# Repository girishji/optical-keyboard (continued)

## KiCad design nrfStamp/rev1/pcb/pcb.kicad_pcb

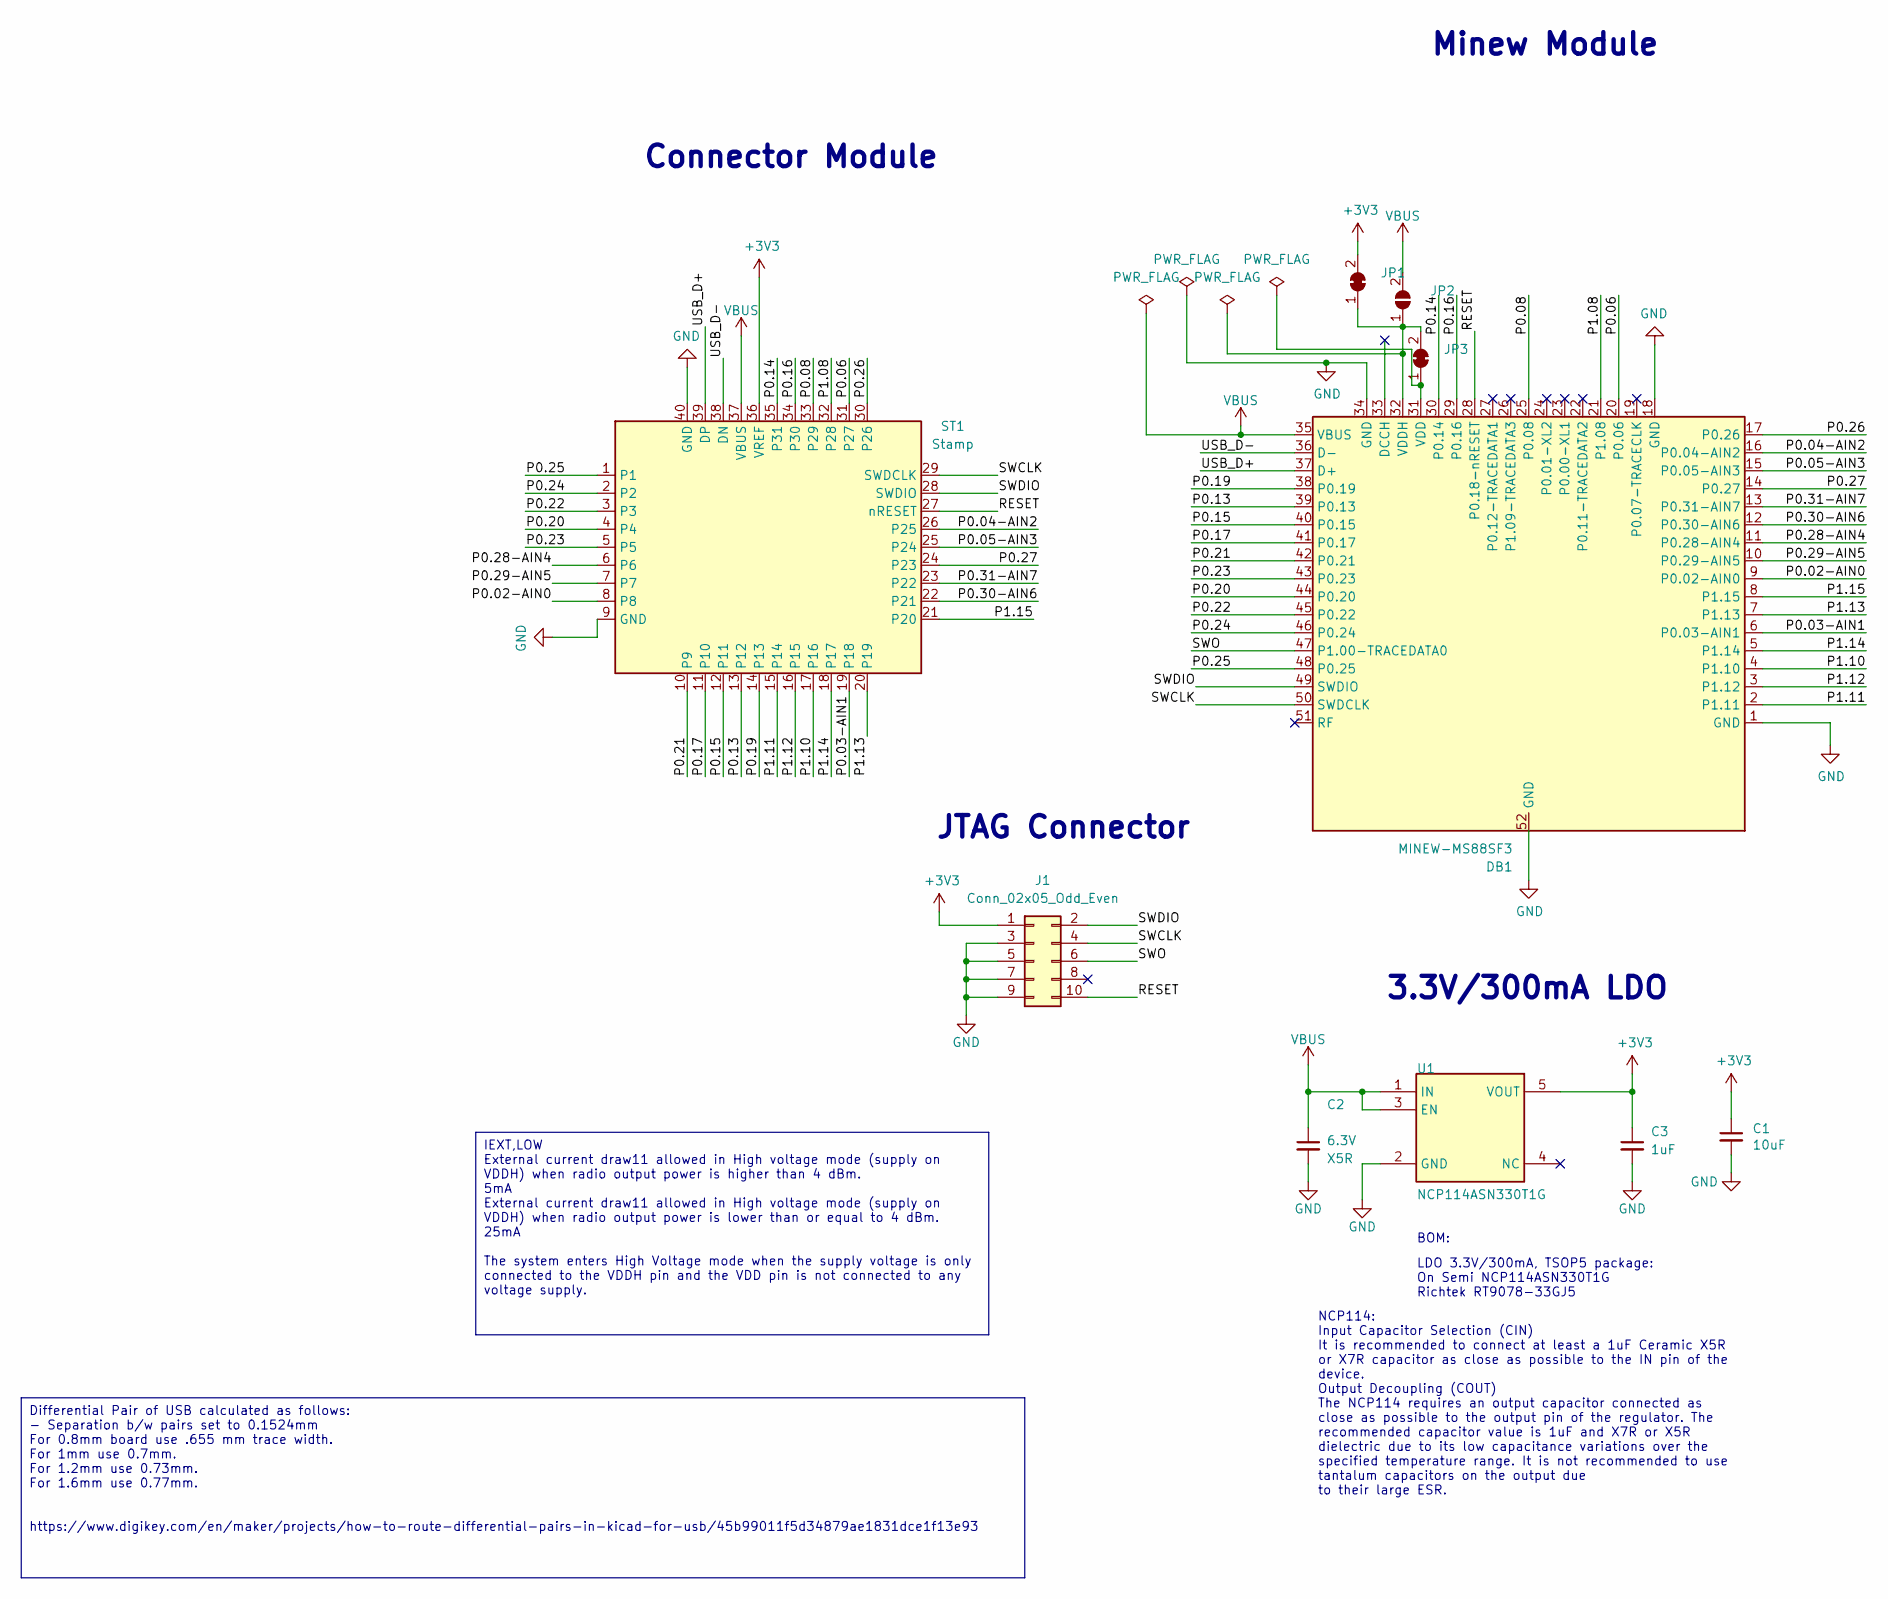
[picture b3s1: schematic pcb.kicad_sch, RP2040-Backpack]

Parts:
C1: 10uF; C_0603_1608Metric; MPN CC0603MRX5R8BB106; LCSC C596327
C2: 2.2uF; C_0603_1608Metric; VOLTAGE RATING 6.3V; TOLERANCE TBD; MPN CL05A225MQ5NNNC; LCSC C107371
C3: 1uF; C_0603_1608Metric; MPN CC0402KRX5R6BB105; LCSC C106254
DB1: MINEW-MS88SF3
J1: Conn_02x05_Odd_Even; PinHeader_2x05_P1.27mm_Horizontal
JP1, JP3: SolderJumper_2_Bridged; SolderJumper-2_Bridged_Pad
JP2: SolderJumper_2_Open; SolderJumper-2_Open_Pad
ST1: Stamp
U1: NCP114ASN330T1G; TSOP-5_1.65x3.05mm_P0.95mm; MPN NCP114ASN330T1G; LCSC C457666

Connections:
+3V3: C1.1, C3.1, J1.1, JP1.2 (B), ST1.36 (VREF), U1.5 (VOUT)
/P0.02-AIN0: DB1.9 (P0.02-AIN0), ST1.8
/P0.03-AIN1: DB1.6 (P0.03-AIN1), ST1.19 (P18)
/P0.04-AIN2: DB1.16 (P0.04-AIN2), ST1.26 (P25)
/P0.05-AIN3: DB1.15 (P0.05-AIN3), ST1.25 (P24)
/P0.06: DB1.20 (P0.06), ST1.31 (P27)
/P0.08: DB1.25 (P0.08), ST1.33 (P29)
/P0.13: DB1.39 (P0.13), ST1.13 (P12)
/P0.14: DB1.30 (P0.14), ST1.35 (P31)
/P0.15: DB1.40 (P0.15), ST1.12 (P11)
/P0.16: DB1.29 (P0.16), ST1.34 (P30)
/P0.17: DB1.41 (P0.17), ST1.11 (P10)
/P0.19: DB1.38 (P0.19), ST1.14 (P13)
/P0.20: DB1.44 (P0.20), ST1.4
/P0.21: DB1.42 (P0.21), ST1.10 (P9)
/P0.22: DB1.45 (P0.22), ST1.3
/P0.23: DB1.43 (P0.23), ST1.5
/P0.24: DB1.46 (P0.24), ST1.2
/P0.25: DB1.48 (P0.25), ST1.1
/P0.26: DB1.17 (P0.26), ST1.30 (P26)
/P0.27: DB1.14 (P0.27), ST1.24 (P23)
/P0.28-AIN4: DB1.11 (P0.28-AIN4), ST1.6
/P0.29-AIN5: DB1.10 (P0.29-AIN5), ST1.7
/P0.30-AIN6: DB1.12 (P0.30-AIN6), ST1.22 (P21)
/P0.31-AIN7: DB1.13 (P0.31-AIN7), ST1.23 (P22)
/P1.08: DB1.21 (P1.08), ST1.32 (P28)
/P1.10: DB1.4 (P1.10), ST1.17 (P16)
/P1.11: DB1.2 (P1.11), ST1.15 (P14)
/P1.12: DB1.3 (P1.12), ST1.16 (P15)
/P1.13: DB1.7 (P1.13), ST1.20 (P19)
/P1.14: DB1.5 (P1.14), ST1.18 (P17)
/P1.15: DB1.8 (P1.15), ST1.21 (P20)
/RESET: DB1.28 (P0.18-nRESET), J1.10, ST1.27 (nRESET)
/SWCLK: DB1.50 (SWDCLK), J1.4, ST1.29 (SWDCLK)
/SWDIO: DB1.49 (SWDIO), J1.2, ST1.28 (SWDIO)
/SWO: DB1.47 (P1.00-TRACEDATA0), J1.6
/USB_D+: DB1.37 (D+), ST1.39 (DP)
/USB_D-: DB1.36 (D-), ST1.38 (DN)
GND: C1.2, C2.2, C3.2, DB1.1 (GND), DB1.18 (GND), DB1.34 (GND), DB1.52 (GND), J1.3, J1.5, J1.7, J1.9, ST1.9 (GND), ST1.40 (GND), U1.2 (GND)
unnamed: DB1.31 (VDD), JP3.1 (A)
unnamed: DB1.32 (VDDH), JP1.1 (A), JP2.1 (A), JP3.2 (B)
VBUS: C2.1, DB1.35 (VBUS), JP2.2 (B), ST1.37 (VBUS), U1.1 (IN), U1.3 (EN)

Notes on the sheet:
IEXT,LOW External current draw11 allowed in High voltage mode (supply on VDDH) when radio output power is higher than 4 dBm. 5mA External current draw11 allowed in High voltage mode (supply on VDDH) when radio output power is lower than or equal to 4 dBm. 25mA The system enters High Voltage mode wh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
Differential Pair of USB calculated as follows: - Separation b/w pairs set to 0.1524mm For 0.8mm board use .655 mm trace width. For 1mm use 0.7mm. For 1.2mm use 0.73mm. For 1.6mm use 0.77mm. https://www.digikey.com/en/maker/projects/how-to-route-differential-pairs-in-kicad-for-usb/45b99011f5d34879a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
3.3V/300mA LDO
JTAG Connector
Connector Module
BOM:
LDO 3.3V/300mA, TSOP5 package: On Semi NCP114ASN330T1G Richtek RT9078-33GJ5
Minew Module
NCP114: Input Capacitor Selection (CIN) It is recommended to connect at least a 1uF Ceramic X5R or X7R capacitor as close as possible to the IN pin of the device. Output Decoupling (COUT) The NCP114 requires an output capacitor connected as close as possible to the output pin of the regulator. The 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

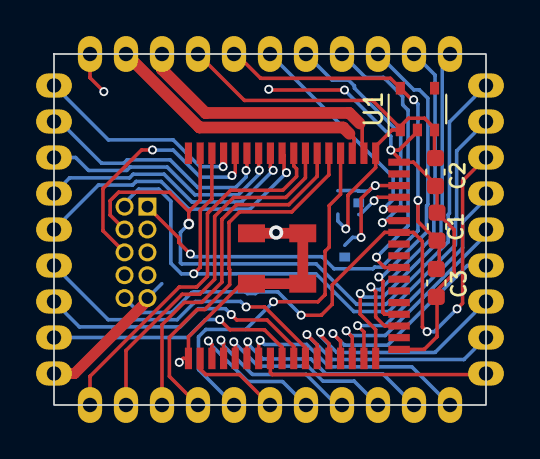
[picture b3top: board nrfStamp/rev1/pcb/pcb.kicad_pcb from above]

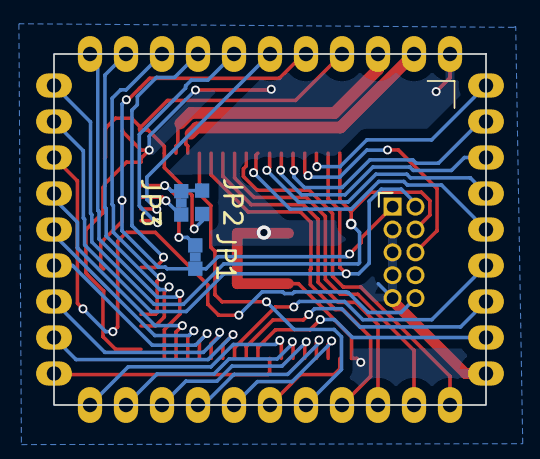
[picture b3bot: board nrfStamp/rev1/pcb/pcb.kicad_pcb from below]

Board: 2 copper layers, 24.0 x 19.5 mm, 10 parts (4 on the bottom side), 42 nets.

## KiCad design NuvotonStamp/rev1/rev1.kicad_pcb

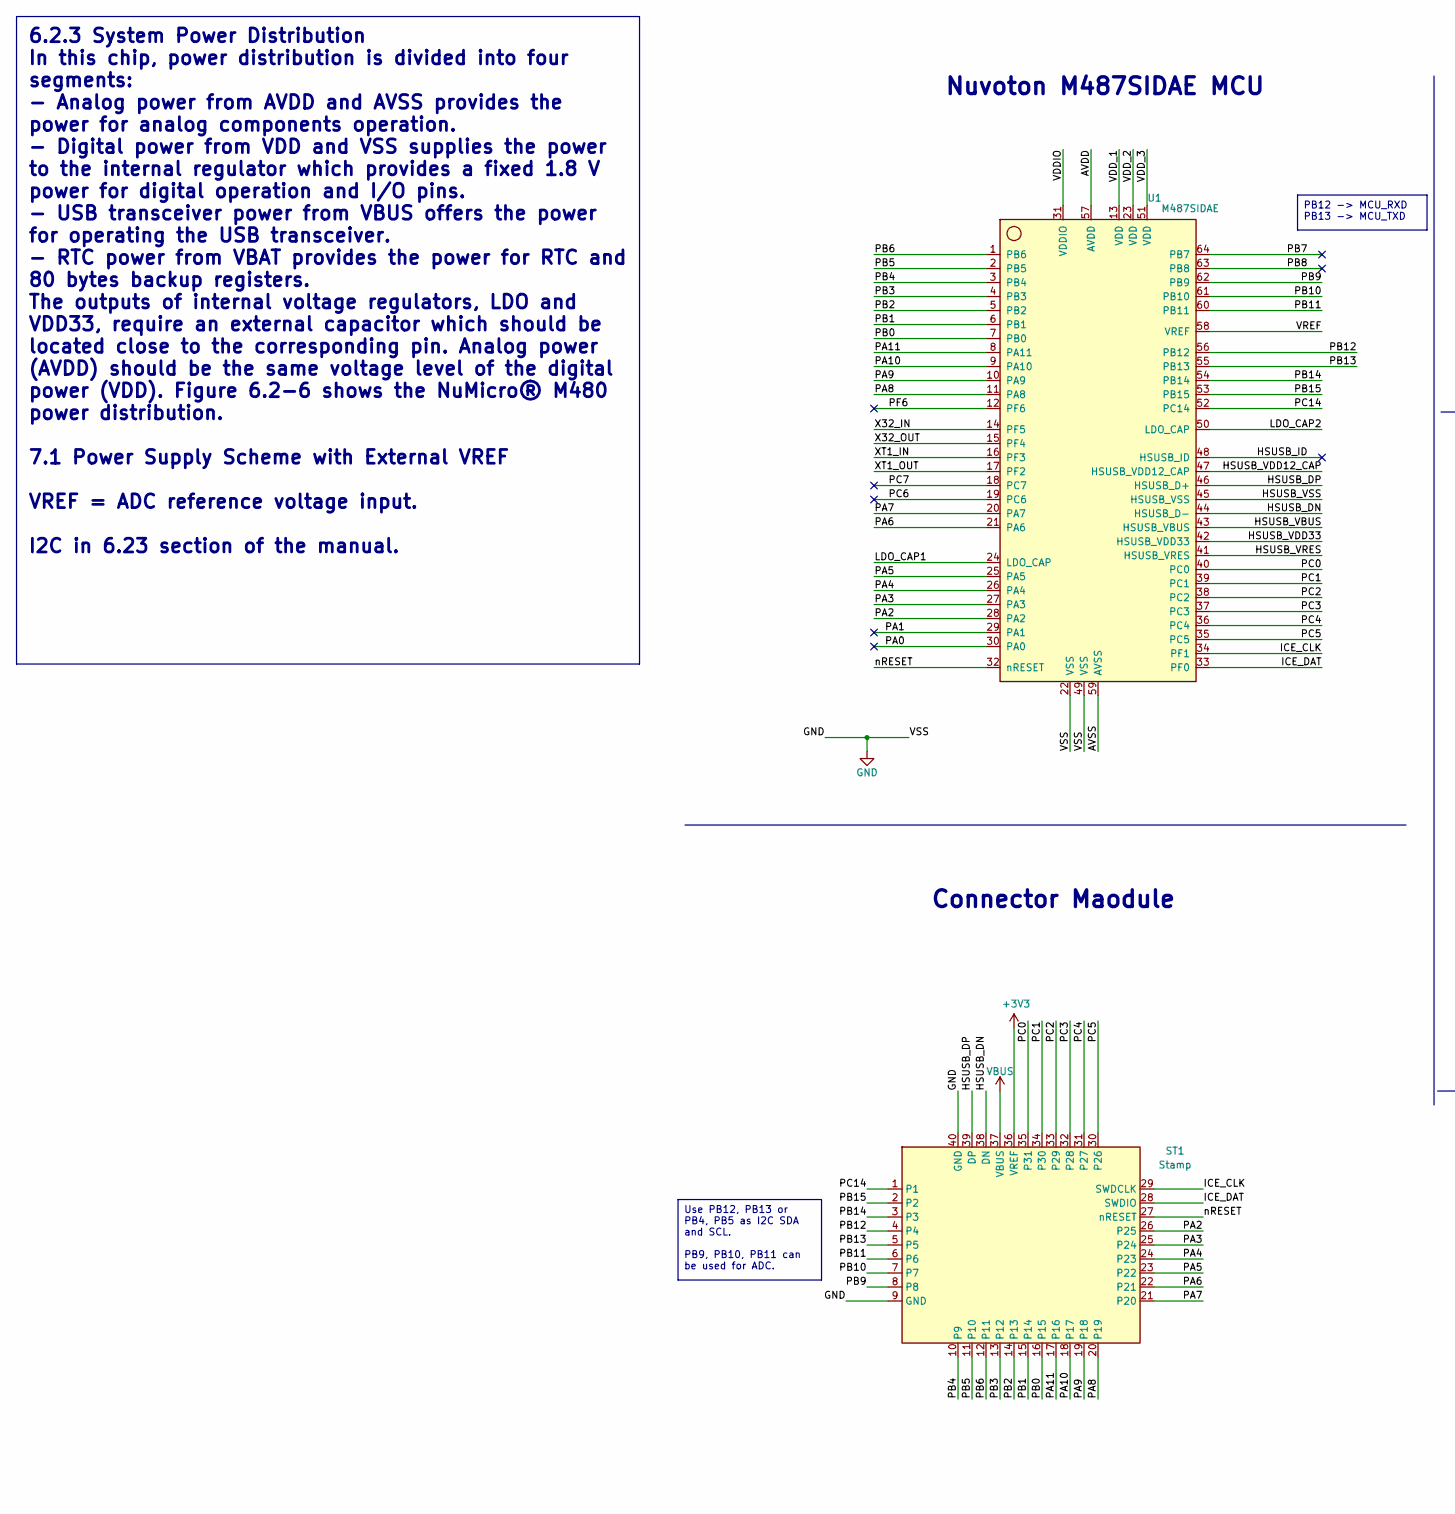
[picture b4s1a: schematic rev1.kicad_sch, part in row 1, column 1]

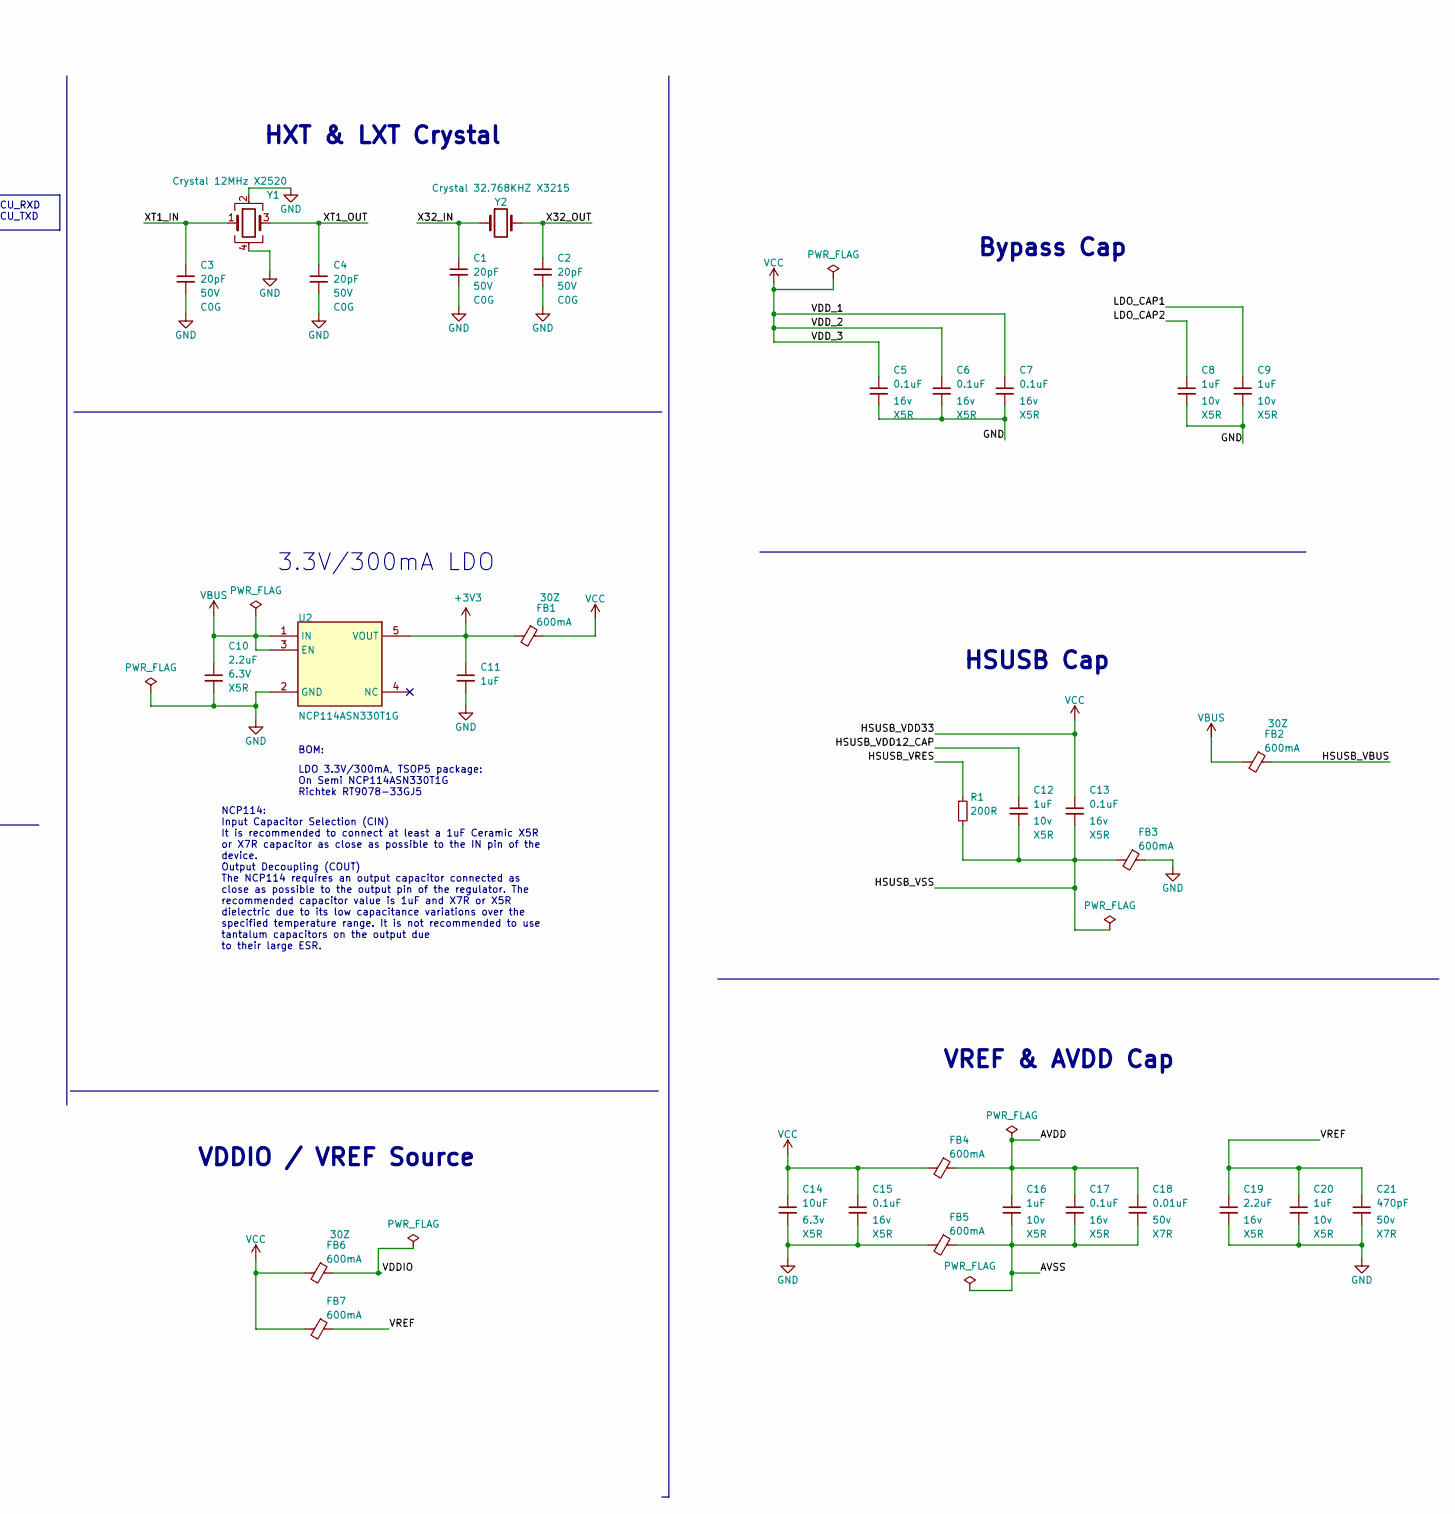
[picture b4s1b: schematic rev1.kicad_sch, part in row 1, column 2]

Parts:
C1, C2, C3, C4: 20pF; C_0402_1005Metric; Voltage Rating 50V; MPN CL05C200JB5NNNC; LCSC C32950
C5, C6, C7, C13, C15, C17: 0.1uF; C_0402_1005Metric; VOLTAGE RATING 16v; MPN CL05B104KO5NNNC; LCSC C1525
C8, C9: 1uF; C_0402_1005Metric; VOLTAGE RATING 10v
C10: 2.2uF; C_0402_1005Metric; VOLTAGE RATING 6.3V; TOLERANCE TBD; MPN CL05A225MQ5NNNC; LCSC C107371
C11: 1uF; C_0402_1005Metric; MPN CC0402KRX5R6BB105; LCSC C106254
C12, C16, C20: 1uF; C_0402_1005Metric; VOLTAGE RATING 10v; MPN CL05A105KP5NNNC; LCSC C14445
C14: 10uF; C_0402_1005Metric; VOLTAGE RATING 6.3v; MPN CL05A106MQ5NUNC; LCSC C15525
C18: 0.01uF; C_0402_1005Metric; VOLTAGE RATING 50v; MPN CL05B103KB5NNNC; LCSC C15195
C19: 2.2uF; C_0402_1005Metric; VOLTAGE RATING 16v; MPN CL05A225KO5NQNC; LCSC C170151
C21: 470pF; C_0402_1005Metric; VOLTAGE RATING 50v; MPN CL05B471KB5NNNC; LCSC C26412
FB1, FB2, FB6: 30Z; R_0402_1005Metric; MPN BLM15AX221SN1D; LCSC C76885
FB3, FB4, FB5, FB7: FerriteBead_Small; R_0402_1005Metric; MPN BLM15AX221SN1D; LCSC C76885
R1: 200R; R_0402_1005Metric; Power Rating 62.5mW; MPN RC0402FR-07200RL; LCSC C114764
ST1: Stamp
U1: M487SIDAE; LQFP-64_7x7mm_P0.4mm
U2: NCP114ASN330T1G; TSOP-5_1.65x3.05mm_P0.95mm; MPN NCP114ASN330T1G; LCSC C457666
Y1: Crystal 12MHz X2520; Crystal_SMD_2520-4Pin_2.5x2.0mm
Y2: Crystal 32.768KHZ X3215; Crystal_SMD_3215-2Pin_3.2x1.5mm; MPN Q13FC1350000200; LCSC C48615

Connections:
+3V3: C11.1, FB1.2, ST1.36 (VREF), U2.5 (VOUT)
/AVDD: C16.1, C17.1, C18.1, FB4.1, U1.57 (AVDD)
/AVSS: C16.2, C17.2, C18.2, FB5.1, U1.59 (AVSS)
/HSUSB_DN: ST1.38 (DN), U1.44 (HSUSB_D-)
/HSUSB_DP: ST1.39 (DP), U1.46 (HSUSB_D+)
/HSUSB_ID: U1.48 (HSUSB_ID)
/HSUSB_VBUS: FB2.1, U1.43 (HSUSB_VBUS)
/HSUSB_VDD12_CAP: C12.1, U1.47 (HSUSB_VDD12_CAP)
/HSUSB_VRES: R1.1, U1.41 (HSUSB_VRES)
/HSUSB_VSS: C12.2, C13.2, FB3.2, R1.2, U1.45 (HSUSB_VSS)
/ICE_CLK: ST1.29 (SWDCLK), U1.34 (PF1)
/ICE_DAT: ST1.28 (SWDIO), U1.33 (PF0)
/LDO_CAP1: C9.1, U1.24 (LDO_CAP)
/LDO_CAP2: C8.1, U1.50 (LDO_CAP)
/PA0: U1.30 (PA0)
/PA1: U1.29 (PA1)
/PA2: ST1.26 (P25), U1.28 (PA2)
/PA3: ST1.25 (P24), U1.27 (PA3)
/PA4: ST1.24 (P23), U1.26 (PA4)
/PA5: ST1.23 (P22), U1.25 (PA5)
/PA6: ST1.22 (P21), U1.21 (PA6)
/PA7: ST1.21 (P20), U1.20 (PA7)
/PA8: ST1.20 (P19), U1.11 (PA8)
/PA9: ST1.19 (P18), U1.10 (PA9)
/PA10: ST1.18 (P17), U1.9 (PA10)
/PA11: ST1.17 (P16), U1.8 (PA11)
/PB0: ST1.16 (P15), U1.7 (PB0)
/PB1: ST1.15 (P14), U1.6 (PB1)
/PB2: ST1.14 (P13), U1.5 (PB2)
/PB3: ST1.13 (P12), U1.4 (PB3)
/PB4: ST1.10 (P9), U1.3 (PB4)
/PB5: ST1.11 (P10), U1.2 (PB5)
/PB6: ST1.12 (P11), U1.1 (PB6)
/PB7: U1.64 (PB7)
/PB8: U1.63 (PB8)
/PB9: ST1.8, U1.62 (PB9)
/PB10: ST1.7, U1.61 (PB10)
/PB11: ST1.6, U1.60 (PB11)
/PB12: ST1.4, U1.56 (PB12)
/PB13: ST1.5, U1.55 (PB13)
/PB14: ST1.3, U1.54 (PB14)
/PB15: ST1.2, U1.53 (PB15)
/PC0: ST1.35 (P31), U1.40 (PC0)
/PC1: ST1.34 (P30), U1.39 (PC1)
/PC2: ST1.33 (P29), U1.38 (PC2)
/PC3: ST1.32 (P28), U1.37 (PC3)
/PC4: ST1.31 (P27), U1.36 (PC4)
/PC5: ST1.30 (P26), U1.35 (PC5)
/PC6: U1.19 (PC6)
/PC7: U1.18 (PC7)
/PC14: ST1.1, U1.52 (PC14)
/PF6: U1.12 (PF6)
/VDDIO: FB6.1, U1.31 (VDDIO)
/VREF: C19.1, C20.1, C21.1, FB7.1, U1.58 (VREF)
/X32_IN: C1.1, U1.14 (PF5), Y2.1
/X32_OUT: C2.1, U1.15 (PF4), Y2.2
/XT1_IN: C3.1, U1.16 (PF3), Y1.1
/XT1_OUT: C4.1, U1.17 (PF2), Y1.3
/nRESET: ST1.27 (nRESET), U1.32 (nRESET)
GND: C1.2, C2.2, C3.2, C4.2, C5.2, C6.2, C7.2, C8.2, C9.2, C10.2, C11.2, C14.2, C15.2, C19.2, C20.2, C21.2, FB3.1, FB5.2, ST1.9 (GND), ST1.40 (GND), U1.22 (VSS), U1.49 (VSS), U2.2 (GND), Y1.2, Y1.4
VBUS: C10.1, FB2.2, ST1.37 (VBUS), U2.1 (IN), U2.3 (EN)
VCC: C5.1, C6.1, C7.1, C13.1, C14.1, C15.1, FB1.1, FB4.2, FB6.2, FB7.2, U1.13 (VDD), U1.23 (VDD), U1.42 (HSUSB_VDD33), U1.51 (VDD)

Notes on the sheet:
PB12 -> MCU_RXD PB13 -> MCU_TXD
Use PB12, PB13 or PB4, PB5 as I2C SDA and SCL. PB9, PB10, PB11 can be used for ADC.
6.2.3 System Power Distribution In this chip, power distribution is divided into four segments: - Analog power from AVDD and AVSS provides the power for analog components operation. - Digital power from VDD and VSS supplies the power to the internal regulator which provides a fixed 1.8 V power for 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
BOM:
3.3V/300mA LDO
Connector Maodule
VREF & AVDD Cap
LDO 3.3V/300mA, TSOP5 package: On Semi NCP114ASN330T1G Richtek RT9078-33GJ5
HSUSB Cap
Nuvoton M487SIDAE MCU
NCP114: Input Capacitor Selection (CIN) It is recommended to connect at least a 1uF Ceramic X5R or X7R capacitor as close as possible to the IN pin of the device. Output Decoupling (COUT) The NCP114 requires an output capacitor connected as close as possible to the output pin of the regulator. The 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
HXT & LXT Crystal
Bypass Cap
VDDIO / VREF Source

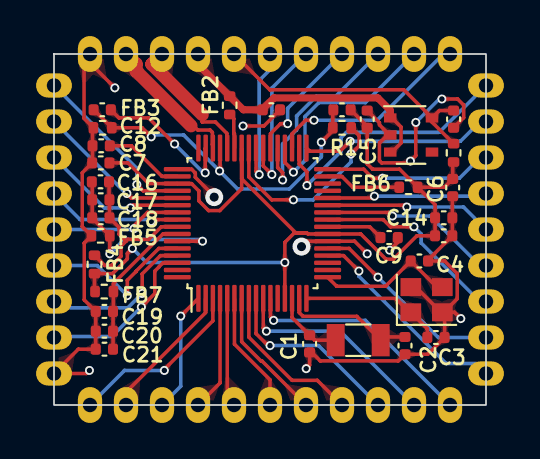
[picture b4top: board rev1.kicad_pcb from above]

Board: 2 copper layers, 24.0 x 19.5 mm, 34 parts (0 on the bottom side), 54 nets.

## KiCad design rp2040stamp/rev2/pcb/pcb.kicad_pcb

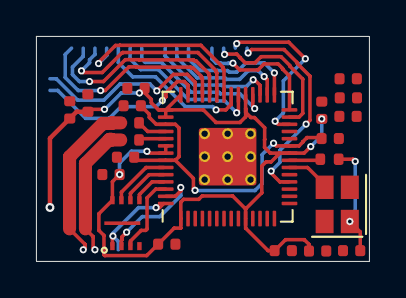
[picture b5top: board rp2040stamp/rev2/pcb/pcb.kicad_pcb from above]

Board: 2 copper layers, 18.5 x 12.5 mm, 23 parts (0 on the bottom side), 35 nets.

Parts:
C1, C2, C3, C4, C5, C6, C7, C8, C9, C12: 100nF; C_0402_1005Metric
C10, C11: 1uF; C_0402_1005Metric
C13: 2.2uF; C_0402_1005Metric
C14, C15: 15pF; C_0402_1005Metric
DB1: MINEW-MS88SF3; MINEW-MS88SF3-Daughter-Board
JLC1: JLC_Order_Num
R1, R2: 27R; R_0402_1005Metric
R3: 1k; R_0402_1005Metric
U1: RP2040; RP2040-QFN-56
U2: Memory_Flash_W25Q64_XSON; 8-USON-Handsolder
X1: 12.000MHz; Crystal_SMD_2520-4Pin_2.5x2.0mm-Handsolder

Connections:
+1V1: C1.1, C2.1, C10.1, U1.23 (DVDD), U1.45 (VREG_VOUT), U1.50 (DVDD)
+3V3: C3.1, C4.1, C5.1, C6.1, C7.1, C8.1, C9.1, C11.1, C12.1, C13.1, DB1.31 (VDD), U1.1 (IOVDD), U1.10 (IOVDD), U1.22 (IOVDD), U1.33 (IOVDD), U1.42 (IOVDD), U1.43 (ADC_AVDD), U1.44 (VREG_IN), U1.48 (USB_VDD), U1.49 (IOVDD), U2.8 (VCC)
/D+: R1.1, U1.47 (USB_DP)
/D-: R2.1, U1.46 (USB_DM)
/GPIO0: DB1.40 (P0.15), U1.2 (GPIO0)
/GPIO15: DB1.2 (P1.11), U1.18 (GPIO15)
/GPIO18: DB1.7 (P1.13), U1.29 (GPIO18)
/GPIO19: DB1.8 (P1.15), U1.30 (GPIO19)
/GPIO20: DB1.9 (P0.02-AIN0), U1.31 (GPIO20)
/GPIO21: DB1.11 (P0.28-AIN4), U1.32 (GPIO21)
/GPIO22: DB1.12 (P0.30-AIN6), U1.34 (GPIO22)
/GPIO23: DB1.13 (P0.31-AIN7), U1.35 (GPIO23)
/GPIO24: DB1.14 (P0.27), U1.36 (GPIO24)
/GPIO25: DB1.15 (P0.05-AIN3), U1.37 (GPIO25)
/GPIO26: DB1.16 (P0.04-AIN2), U1.38 (GPIO26_ADC0)
/GPIO27: DB1.17 (P0.26), U1.39 (GPIO27_ADC1)
/GPIO28: DB1.20 (P0.06), U1.40 (GPIO28_ADC2)
/GPIO29: DB1.21 (P1.08), U1.41 (GPIO29_ADC3)
/QSPI_SCLK: U1.52 (QSPI_SCLK), U2.6 (CLK)
/QSPI_SD0: U1.53 (QSPI_SD0), U2.5 (DI_(IO0))
/QSPI_SD1: U1.55 (QSPI_SD1), U2.2 (DO_(IO1))
/QSPI_SD2: U1.54 (QSPI_SD2), U2.3 (~WP_(IO2))
/QSPI_SD3: U1.51 (QSPI_SD3), U2.7 (~HOLD_(IO3))
/QSPI_SS: DB1.39 (P0.13), U1.56 (QSPI_SS), U2.1 (~{CS)
/RUN: DB1.3 (P1.12), U1.26 (RUN)
/SWCLK: DB1.50 (SWDCLK), U1.24 (SWCLK)
/SWD: DB1.49 (SWDIO), U1.25 (SWD)
/USB_D+: DB1.37 (D+), R1.2
/USB_D-: DB1.36 (D-), R2.2
/XIN: C15.1, U1.20 (XIN), X1.3
/XOUT: R3.1, U1.21 (XOUT)
GND: C1.2, C2.2, C3.2, C4.2, C5.2, C6.2, C7.2, C8.2, C9.2, C10.2, C11.2, C12.2, C13.2, C14.2, C15.2, DB1.1 (GND), DB1.18 (GND), DB1.34 (GND), DB1.56 (GND), U1.19 (TESTEN), U1.57 (GND), U2.4 (GND), U2.9 (EP), X1.2, X1.4
unnamed: C14.1, R3.2, X1.1
SCL: DB1.5 (P1.14), U1.28 (GPIO17)
SDA: DB1.4 (P1.10), U1.27 (GPIO16)

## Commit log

2022-10-13 First commit
    A .DS_Store
    A Giri_Library.kicad_sym
    A Giri_Library.pretty/Keychron_Optical_Switch_1u.kicad_mod
    A Giri_Library.pretty/SMTSO_M2.kicad_mod
    A Giri_Library.pretty/Switch_Cutout_LoPro.kicad_mod
    A Giri_Library.pretty/Switch_Cutout_LoPro_2.25u_Faulty.kicad_mod
2022-10-14 M .gitignore M lopro/drawborderk.py M lopro/pcb/pcb.kicad_pcb M lopro/pcb/pcb.kicad_sch M lopro/place_fp.py
2022-10-14 removed zip
    M .gitignore
    D lopro/pcb/pcb-backups/pcb-2022-10-13_182503.zip
    D lopro/pcb/pcb-backups/pcb-2022-10-13_183133.zip
    D lopro/pcb/pcb-backups/pcb-2022-10-13_202552.zip
    D lopro/pcb/pcb-backups/pcb-2022-10-13_212841.zip
    D lopro/pcb/pcb-backups/pcb-2022-10-13_213616.zip
2022-10-14 A lopro/pcb/.gitignore
2022-10-14 updated
    M lopro/drawborderk.py
2022-10-14 bug fix
    M lopro/drawborderk.py
2022-10-14 added tracks
    M Giri_Library.pretty/Keychron_Optical_Switch_1u.kicad_mod
    D lopro/drawborder.py
    M lopro/pcb/pcb.kicad_pcb
    M lopro/pcb/pcb.kicad_prl
    M lopro/place_fp.py
2022-10-15 add tracks
    M Giri_Library.kicad_sym
    M Giri_Library.pretty/Keychron_Optical_Switch_1u.kicad_mod
    A lopro/pcb/LED-Driver.kicad_sch
    M lopro/pcb/pcb.kicad_pcb
    M lopro/pcb/pcb.kicad_sch
    M lopro/place_fp.py
2022-10-16 gitignore
    A lopro/switch-plate/.gitignore
2022-10-16 add 1-1/4 key
    M lopro/place_fp.py
2022-10-17 add new pcb for rp2040 30 pin mcu
    R lopro/drawborderk.py -> lopro/6banks/drawborderk.py
    R lopro/pcb/.gitignore -> lopro/6banks/pcb/.gitignore
    R lopro/pcb/LED-Driver.kicad_sch -> lopro/6banks/pcb/LED-Driver.kicad_sch
    R lopro/pcb/fp-lib-table -> lopro/6banks/pcb/fp-lib-table
    R lopro/pcb/pcb.kicad_pcb -> lopro/6banks/pcb/pcb.kicad_pcb
    R lopro/pcb/pcb.kicad_prl -> lopro/6banks/pcb/pcb.kicad_prl
2022-10-27 Added new keyboard
    D .DS_Store
    A giri-kicad-lib/.gitignore
    R Giri_Library.kicad_sym -> giri-kicad-lib/switches.kicad_sym
    A giri-kicad-lib/switches_lib.pretty/C_0402_1005Metric.kicad_mod
    A giri-kicad-lib/switches_lib.pretty/C_0603_1608Metric.kicad_mod
    A giri-kicad-lib/switches_lib.pretty/C_1206_3216Metric.kicad_mod
2022-10-27 Add images
    M lopro/8rows/drawborder8b.py
    A lopro/8rows/pcb/pcb-b.png
    A lopro/8rows/pcb/pcb-f.png
    M lopro/8rows/pcb/pcb.kicad_pcb
    M lopro/8rows/pcb/pcb.kicad_sch
2022-10-28 add wrist support
    M giri-kicad-lib/switches.kicad_sym
    A giri-kicad-lib/switches_lib.pretty/MountingHole_1.7mm_M1.6_NoPad.kicad_mod
    M giri-kicad-lib/switches_lib.pretty/Pad_Only_SMTSO_M2.kicad_mod
    A giri-kicad-lib/switches_lib.pretty/SMTSO_M2_Hole_Only.kicad_mod
    M giri-kicad-lib/switches_lib.pretty/Switch_Cutout_LoPro.kicad_mod
    A giri-kicad-lib/switches_lib.pretty/Switch_Cutout_LoPro_R.kicad_mod
2022-11-03 add tracks
    M giri-kicad-lib/switches.kicad_sym
    A giri-kicad-lib/switches_lib.pretty/JLC_Order_Num.kicad_mod
    A lopro/8rows/border8r.py
    M lopro/8rows/pcb/pcb.kicad_pcb
    M lopro/8rows/pcb/pcb.kicad_prl
    M lopro/8rows/pcb/pcb.kicad_pro
2022-12-06 enlarge center hole of keychron switch footprint
    M giri-kicad-lib/switches.kicad_sym
    M giri-kicad-lib/switches_lib.pretty/Keychron_Optical_Switch_1u.kicad_mod
    M giri-kicad-lib/switches_lib.pretty/Keychron_Optical_Switch_R_1u.kicad_mod
    A giri-kicad-lib/switches_lib.pretty/USB_C_Receptacle_Outline_XKB_U262-16XN-4BVC11.kicad_mod
    M lopro/8rows/border8r.py
    D lopro/8rows/pcb/jlcpcb/gerbers/pcb-B_Cu.gbl
2023-05-12 prototype
    M giri-kicad-lib/switches.kicad_sym
    A giri-kicad-lib/switches_lib.pretty/Everlight_IR_IR12-21C_TR8.kicad_mod
    A giri-kicad-lib/switches_lib.pretty/Everlight_PT_PT12-21C_TR8.kicad_mod
    A giri-kicad-lib/switches_lib.pretty/Gateron_Sw_1u.kicad_mod
    A giri-kicad-lib/switches_lib.pretty/LED_RGB_PLCC4.kicad_mod
    A giri-kicad-lib/switches_lib.pretty/RS-1515MBAM-RGB_LED.kicad_mod
2023-09-28 M giri-kicad-lib/switches.kicad_sym A giri-kicad-lib/switches_lib.pretty/Gateron_1u.kicad_mod A giri-kicad-lib/switches_lib.pretty/LED_0603_1608Metric.kicad_mod A giri-kicad-lib/switches_lib.pretty/L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
2023-09-28 M .gitignore D mx/rev3/switch-plate/jlcpcb/gerbers/switch-plate-B_Cu.gbl D mx/rev3/switch-plate/jlcpcb/gerbers/switch-plate-B_Mask.gbs D mx/rev3/switch-plate/jlcpcb/gerbers/switch-plate-B_Paste.gbp D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
2023-09-29 M .gitignore M giri-kicad-lib/switches.kicad_sym A giri-kicad-lib/switches_lib.pretty/RP2040_Stamp.kicad_mod A giri-kicad-lib/switches_lib.pretty/SW_B3U-3000P.kicad_mod M lopro/8rows/pcb/pcb.kicad_sc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
2023-09-30 A giri-kicad-lib/switches_lib.pretty/WristExtension.kicad_mod D mx/rev3/.border.py.swp D mx/rev3/.build.py.swp M mx/rev3/build.py M mx/rev3/pcb/pcb.kicad_prl
2023-10-01 s
    M mx/rev3/build.py
    D mx/rev3/test.py
2023-10-01 M mx/rev3/.gitignore M mx/rev3/border.py M mx/rev3/build.py M mx/rev3/pcb/pcb.kicad_prl
2023-10-02 M mx/rev3/border.py
2023-10-02 M mx/rev3/border.py M mx/rev3/build.py
2023-10-03 M mx/rev3/border.py M mx/rev3/pcb/pcb.kicad_pcb M mx/rev3/pcb/pcb.kicad_prl M mx/rev3/pcb/pcb.kicad_sch RM mx/rev3/build.py -> mx/rev3/place.py
2023-10-04 M giri-kicad-lib/switches.kicad_sym M giri-kicad-lib/switches_lib.pretty/PGA2040_SMT_WITH_SLOT.kicad_mod M mx/rev3/border.py M mx/rev3/pcb/pcb.kicad_pcb M mx/rev3/pcb/pcb.kicad_prl M mx/rev3/pcb/pcb.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
2023-10-07 M giri-kicad-lib/switches.kicad_sym M giri-kicad-lib/switches_lib.pretty/Gateron_1u.kicad_mod M giri-kicad-lib/switches_lib.pretty/Gateron_Sw_1u.kicad_mod M giri-kicad-lib/switches_lib.pretty/PGA2040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
2023-10-14 M giri-kicad-lib/switches.kicad_sym M giri-kicad-lib/switches_lib.pretty/C_0603_1608Metric.kicad_mod M giri-kicad-lib/switches_lib.pretty/Gateron_1u.kicad_mod M giri-kicad-lib/switches_lib.pretty/Gat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
2023-10-18 A NuvotonStamp/rev1/fp-lib-table A NuvotonStamp/rev1/rev1.kicad_pcb A NuvotonStamp/rev1/rev1.kicad_prl R mx/rev3/wrist-washer/wrist-washer.kicad_pro -> NuvotonStamp/rev1/rev1.kicad_pro A NuvotonStamp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
2024-07-08 M giri-kicad-lib/switches_lib.pretty/Gateron_1.25u_v2.kicad_mod M giri-kicad-lib/switches_lib.pretty/Gateron_1u_v2.kicad_mod M giri-kicad-lib/switches_lib.pretty/Gateron_2u_v2.kicad_mod A giri-kicad-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
2025-02-20 M mx/rev4/notes
2025-11-09 A remove_tracks.py
2026-04-06 A giri-kicad-lib/RP2040_Minimal.kicad_sym A giri-kicad-lib/RP2040_minimal.pretty/8-USON-Handsolder.kicad_mod A giri-kicad-lib/RP2040_minimal.pretty/8-USON.kicad_mod A giri-kicad-lib/RP2040_minimal.pr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
